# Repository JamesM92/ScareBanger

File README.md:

# ScareBanger
The ScareBanger is intended to be an all around arduino breakout board, intended primarily for use with relay boards in haunted house prop control using the octobanger gui prop control software. 

It is desigend to connect directly to sainsmart 4/8 ch  or HiLetGo 1/2/4/8 ch relay boards to reduce the need for wiring. While providing access to the pins needed for I2C, SPI, RX/TX, interrupt, and analog pins that may be needed for more advanced projects.

Features  
  -5.5mmx2.5mm barrel jack connector for 12V power supply.  
  -screw terminals for 3.3V, 5V, and 12V power to connect to peripheral devices.  
  -All pluggable connections are verticcal to reduce the side space needed when placing board inside a project box.  
  -The board has a RJ45 8p8c connector that allows connection to +12V power, RX/TX lines and reset pin for serial communication.  
  -Sainsmart Relay board connection to 4ch / 8ch using 6 pin / 10 pin female headers  
  -HiLetGo Relay board conenctions 1ch/2ch/4ch/8ch using 5mm spaced right angle headers.  

# Dependencies  
-kiCad V6 Default Libraries  
-Digikey part library -> https://www.digikey.com/en/resources/design-tools/kicad

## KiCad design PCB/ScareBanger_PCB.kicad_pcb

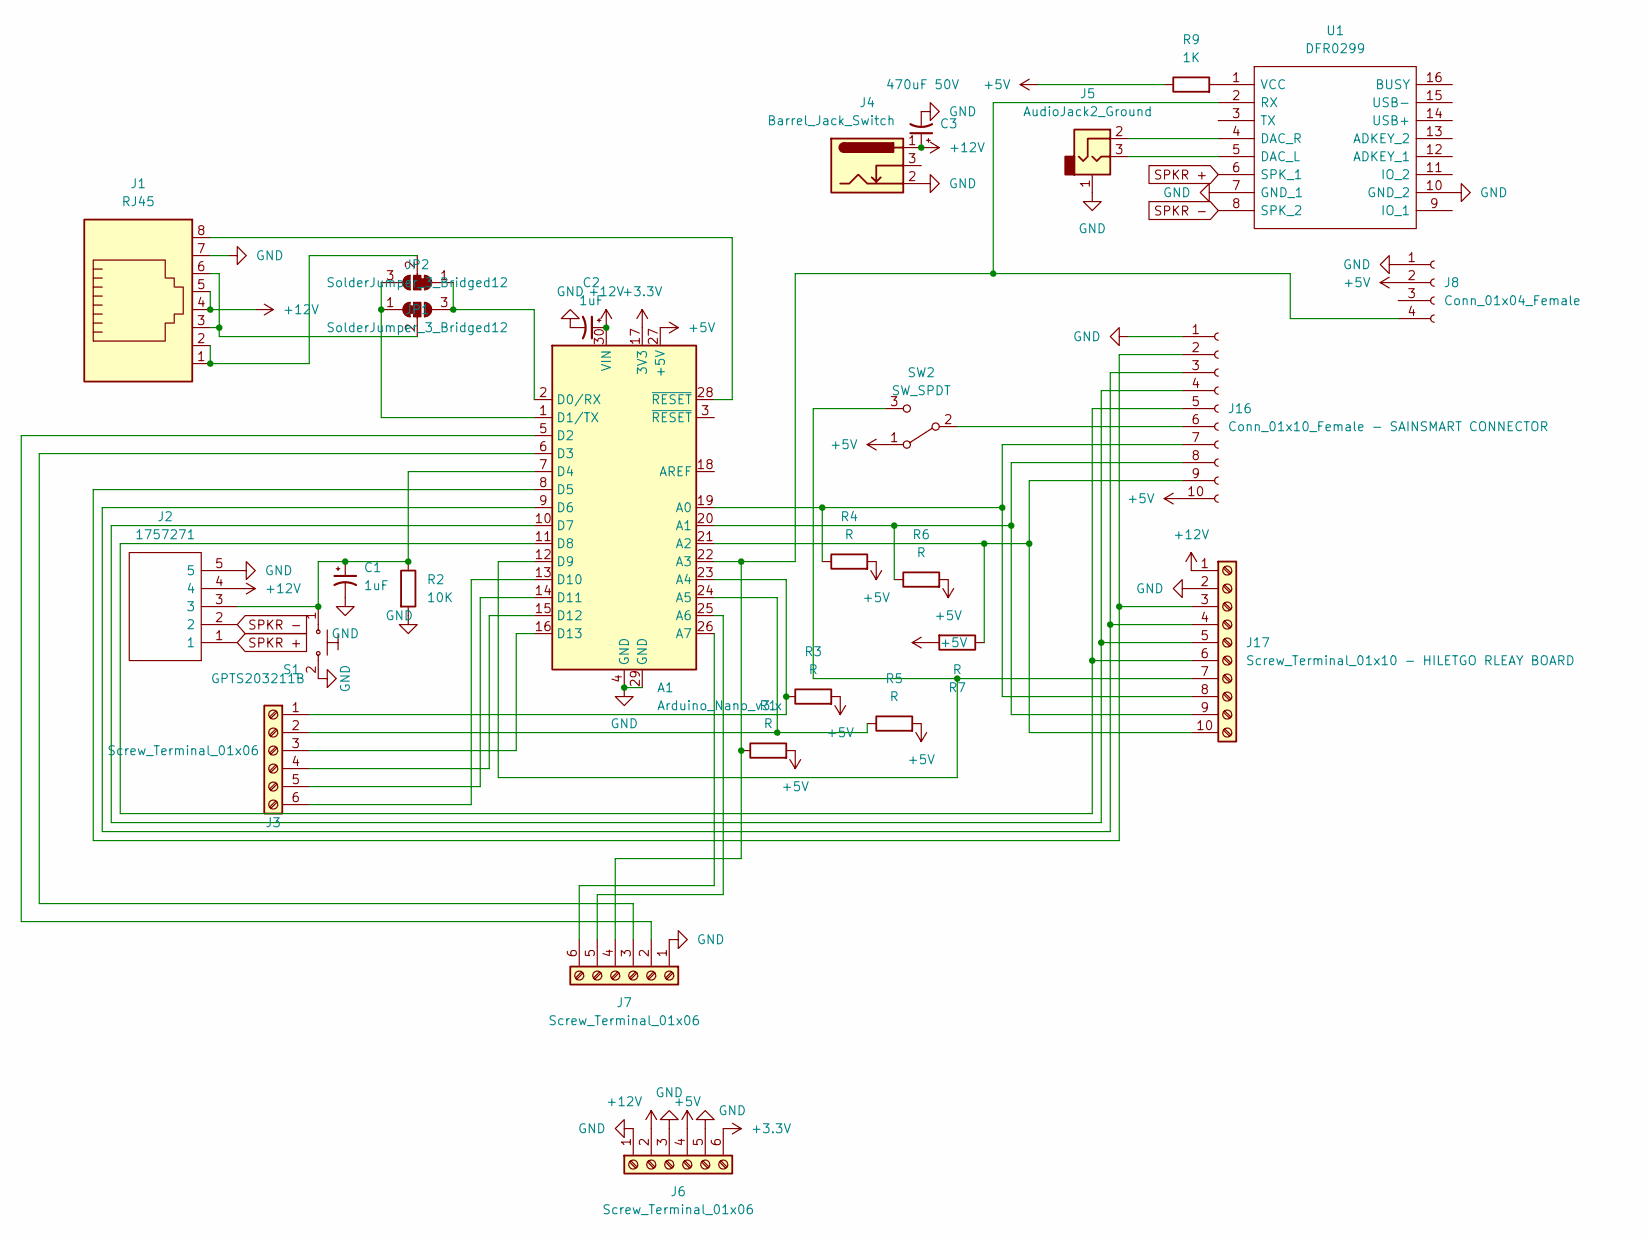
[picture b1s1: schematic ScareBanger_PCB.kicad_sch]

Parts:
A1: Arduino_Nano_v3.x; ARDNANO30NP
C1, C2: 1uF; CP_Radial_D4.0mm_P1.50mm
C3: 470uF 50V; CP_Radial_D8.0mm_P3.50mm
J1: RJ45; 54602908LF
J2: 1757271; 691311500105; Manufacturer_Part_Number 1757271; Mouser Part Number 651-1757271
J3, J6, J7: Screw_Terminal_01x06; TerminalBlock_bornier-6_P5.08mm
J4: Barrel_Jack_Switch; Vertical-BarrelJack_54-00287
J5: AudioJack2_Ground; PJ-301C HeadPhoneJack
J8: Conn_01x04_Female; PinHeader_1x04_P2.54mm_Vertical
J16: Conn_01x10_Female - SAINSMART CONNECTOR; PinSocket_1x10_P2.54mm_Vertical
J17: Screw_Terminal_01x10 - HILETGO RLEAY BOARD; PinHeader_1x10_P5.0mm_Horizontal
JP1, JP2: SolderJumper_3_Bridged12; SolderJumper-3_P1.3mm_Bridged12_Pad1.0x1.5mm
R1, R3, R4, R5, R6, R7: R; R_Axial_DIN0207_L6.3mm_D2.5mm_P2.54mm_Vertical
R2: 10K; R_Axial_DIN0207_L6.3mm_D2.5mm_P2.54mm_Vertical
R9: 1K; R_Axial_DIN0207_L6.3mm_D2.5mm_P7.62mm_Horizontal
S1: GPTS203211B; SW_PUSH_6mm; MPN GPTS203211B; Digi-Key_PN CW181-ND
SW2: SW_SPDT; SpDt SlideSwitch
U1: DFR0299; DIPS1778W50P254L2100H170Q16N; Manufacturer_Part_Number DFR0299; Mouser Part Number 426-DFR0299

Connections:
+3.3V: A1.17 (3V3), J6.6
+5V: A1.27 (+5V), J6.4, J8.2, J16.10, R1.2, R3.2, R4.2, R5.2, R6.2, R7.2, R9.1, SW2.1 (A)
+12V: A1.30 (VIN), C2.1, C3.1, J1.4, J1.5, J2.4, J4.1, J6.2, J17.1
GND: A1.4 (GND), A1.29 (GND), C1.2, C2.2, C3.2, J1.7, J2.5, J4.2, J5.1, J6.1, J6.3, J6.5, J7.1, J8.1, J16.1, J17.2, R2.2, S1.2, U1.7 (GND_1), U1.10 (GND_2)
unnamed: A1.1 (D1/TX), JP1.3 (B), JP2.1 (A)
unnamed: A1.2 (D0/RX), JP1.1 (A), JP2.3 (B)
unnamed: A1.5 (D2), J7.2
unnamed: A1.6 (D3), J7.3
unnamed: A1.7 (D4), C1.1, J2.3, R2.1, S1.1
unnamed: A1.8 (D5), J16.2, J17.3
unnamed: A1.9 (D6), J16.3, J17.4
unnamed: A1.10 (D7), J16.4, J17.5
unnamed: A1.11 (D8), J16.5, J17.6
unnamed: A1.12 (D9), J17.7, SW2.3 (C)
unnamed: A1.13 (D10), J3.6
unnamed: A1.14 (D11), J3.5
unnamed: A1.15 (D12), J3.4
unnamed: A1.16 (D13), J3.3
unnamed: A1.19 (A0), J16.7, J17.8, R4.1
unnamed: A1.20 (A1), J16.8, J17.9, R6.1
unnamed: A1.21 (A2), J16.9, J17.10, R7.1
unnamed: A1.22 (A3), J7.4, J8.4, R1.1, U1.2 (RX)
unnamed: A1.23 (A4), J3.1, R3.1
unnamed: A1.24 (A5), J3.2, R5.1
unnamed: A1.25 (A6), J7.5
unnamed: A1.26 (A7), J7.6
unnamed: A1.28 (~RESET), J1.8
unnamed: J1.1, J1.2, JP1.2 (C)
unnamed: J1.3, J1.6, JP2.2 (C)
unnamed: J5.2, U1.4 (DAC_R)
unnamed: J5.3, U1.5 (DAC_L)
unnamed: J16.6, SW2.2 (B)
unnamed: R9.2, U1.1 (VCC)
SPKR +: J2.1, U1.6 (SPK_1)
SPKR -: J2.2, U1.8 (SPK_2)

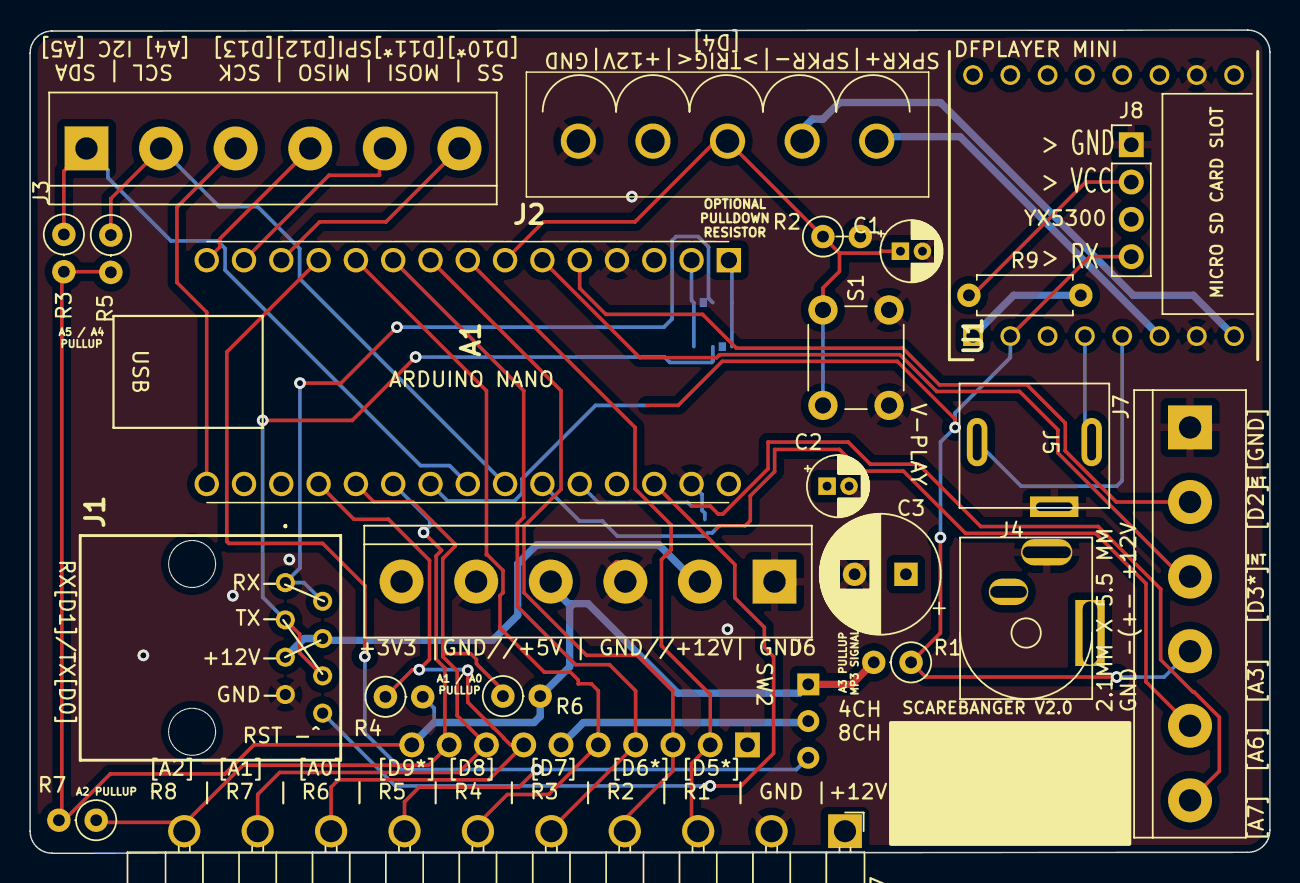
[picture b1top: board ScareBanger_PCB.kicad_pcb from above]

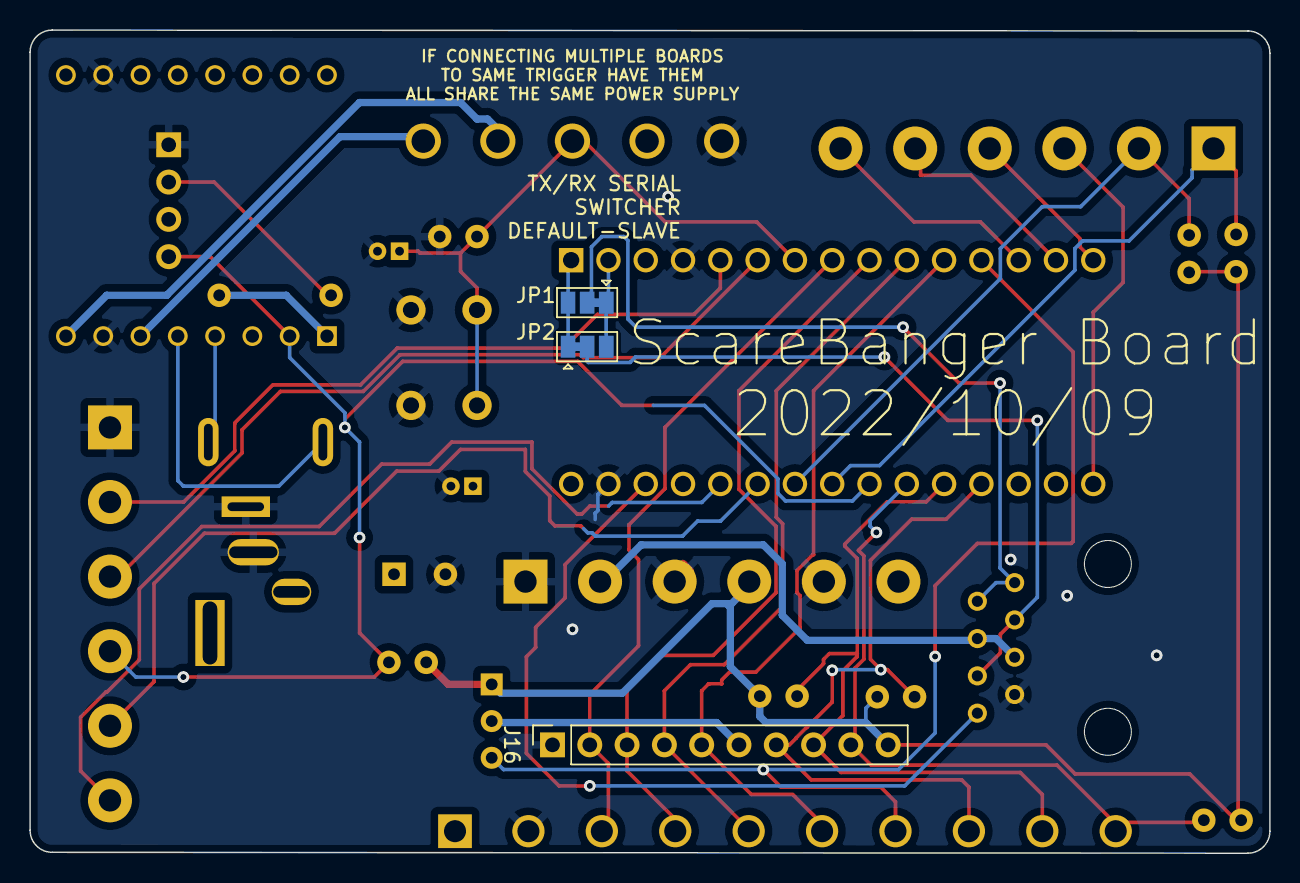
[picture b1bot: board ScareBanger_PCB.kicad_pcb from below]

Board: 4 copper layers, 84.4 x 56.1 mm, 27 parts (3 on the bottom side), 35 nets.

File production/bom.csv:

Designator,Footprint,Quantity,Value,LCSC Part #
A1,ARDNANO30NP,1,Arduino_Nano_v3.x,
J3,TerminalBlock_bornier-6_P5.08mm,1,Screw_Terminal_01x06,
SW2,SpDt SlideSwitch,1,SW_SPDT,
J6,TerminalBlock_bornier-6_P5.08mm,1,Screw_Terminal_01x06,
J7,TerminalBlock_bornier-6_P5.08mm,1,Screw_Terminal_01x06,
J2,691311500105,1,1757271,
S1,SW_PUSH_6mm,1,GPTS203211B,GPTS203211B
J17,PinHeader_1x10_P5.0mm_Horizontal,1,Screw_Terminal_01x10 -  HILETGO RLEAY BOARD,
R2,R_Axial_DIN0516_L15.5mm_D5.0mm_P5.08mm_Vertical,1,10K,
J1,54602908LF,1,RJ45,
SW1,SpDt SlideSwitch,1,SW_SPDT,
J4,Vertical-BarrelJack_54-00287,1,Barrel_Jack_Switch,
J16,PinSocket_1x10_P2.54mm_Vertical,1,Conn_01x10_Female - SAINSMART CONNECTOR,
JP1,SolderJumper-3_P1.3mm_Bridged12_Pad1.0x1.5mm,1,SolderJumper_3_Bridged12,
JP2,SolderJumper-3_P1.3mm_Bridged12_Pad1.0x1.5mm,1,SolderJumper_3_Bridged12,

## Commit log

2022-10-05 Initial Commit
    initial Commit of pcb design
2022-10-05 updated pdf
2022-10-05 updated pdf of layers
2022-10-06 Trigger pin changed to D4
    trigger pin switched from D9 to D4 so D9 with its PWM is available for outputs
2022-10-06 added graphic for pin assignment
2022-10-06 Combined with code
    Combined Code with PCB repositiory under the PCB repository. to simplify version control
2022-10-09 add mp3 module
    added mp3 module, both dfplayer and yx5300 options, re-did layout for the mp3 player and the headphone jack options.
2022-10-11 ADDED MOUNTING HOLES
    ADDED 2 MOUNTING HOLES TO BOARD.
2022-10-11 added mounting holes
    added mounting holes and updated gerber and bom
2023-02-06 minor update
    previous commit had minor corruption, resubmitting
2023-02-11 added signal cap
    added capacitor for signal wire, and changed the main 12v trace to be 2mm wide
2023-02-11 corrected some wire routing
2023-02-11 4 layer update
